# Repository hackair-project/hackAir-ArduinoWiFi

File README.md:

hackAIR is an EU-funded project aiming to develop an open technology platform for citizen observatories on air quality. Air pollution is an environmental issue with serious health and lifespan implications. However, it remains difficult for citizens to assess their exposure to air pollution and air quality issues in their country. Official air quality sensors are often few and far between, coverage is poor outside cities, and their data is not always easily accessible.

## hackAIR WiFi shield

The hackAIR WiFi shield is a do-it-yourself solution for adding wireless connectivity to an Arduino node on the cheap. It's based around a custom PCB and the ESP8266 WiFi module and it's supported by the hackAIR firmware. All the network-related work is done by the WiFi module that can be controlled by simple serial commands. The [hackAIR library for Arduino](https://github.com/hackair-project/hackAir-Arduino) contains helpful wrapper functions to make using the shield easy and simple.

### Where to order

PCBs can be ordered directly from OSHPark [here](https://oshpark.com/shared_projects/u7Z6d8GR). The source files are included in this repository so anyone can order from their manufacturer of choice. Work is being done  to make complete kits available soon.

### Documentation

Documentation for this shield is under construction [here](https://hackair-project.github.io/hackAir-Arduino/wifi/).

### Technicalities

The PCB is designed using the open source EDA called [KiCad](http://kicad-pcb.org/). The PCB render shown above is created using [PcbDraw](https://github.com/yaqwsx/PcbDraw).

### Changelog

#### Version 2.2

* Fix silkscreen of transistor Q1
* Remove footprint for ESP-12
* Add silkscreen for the programming header (pin numbers and names)

#### Version 2
 - [Add] Pull-down resistor for pin 2 (ESP Reset) so the user can flash the Arduino without jumpers
 - [Add] Silkscreen markings for pin numbers
 - [Add] Programming header for the WiFi module
 - [Del] Removed sensor I/O header used by analog sensors
 - [Del] Removed the RC filter required by some analog sensors by SHARP
 - [Fix] Move some decoupling capacitors closer to the power pads
 - [Fix] Moved the CONN_POWER and CONN_SERIAL connectors away from the USB connector of the Arduino board
 - [Fix] Fixed some acid traps in the routing
 - [Fix] Fixed the footprint of Q1 (DSG -> DGS)
 - [Fix] Changed the foorprints of all non-electrolytic caps to be wider.
 - [Fix] Fixed the silkscreen of U1 appearing on the wrong layer.

#### Version 1
Initial release

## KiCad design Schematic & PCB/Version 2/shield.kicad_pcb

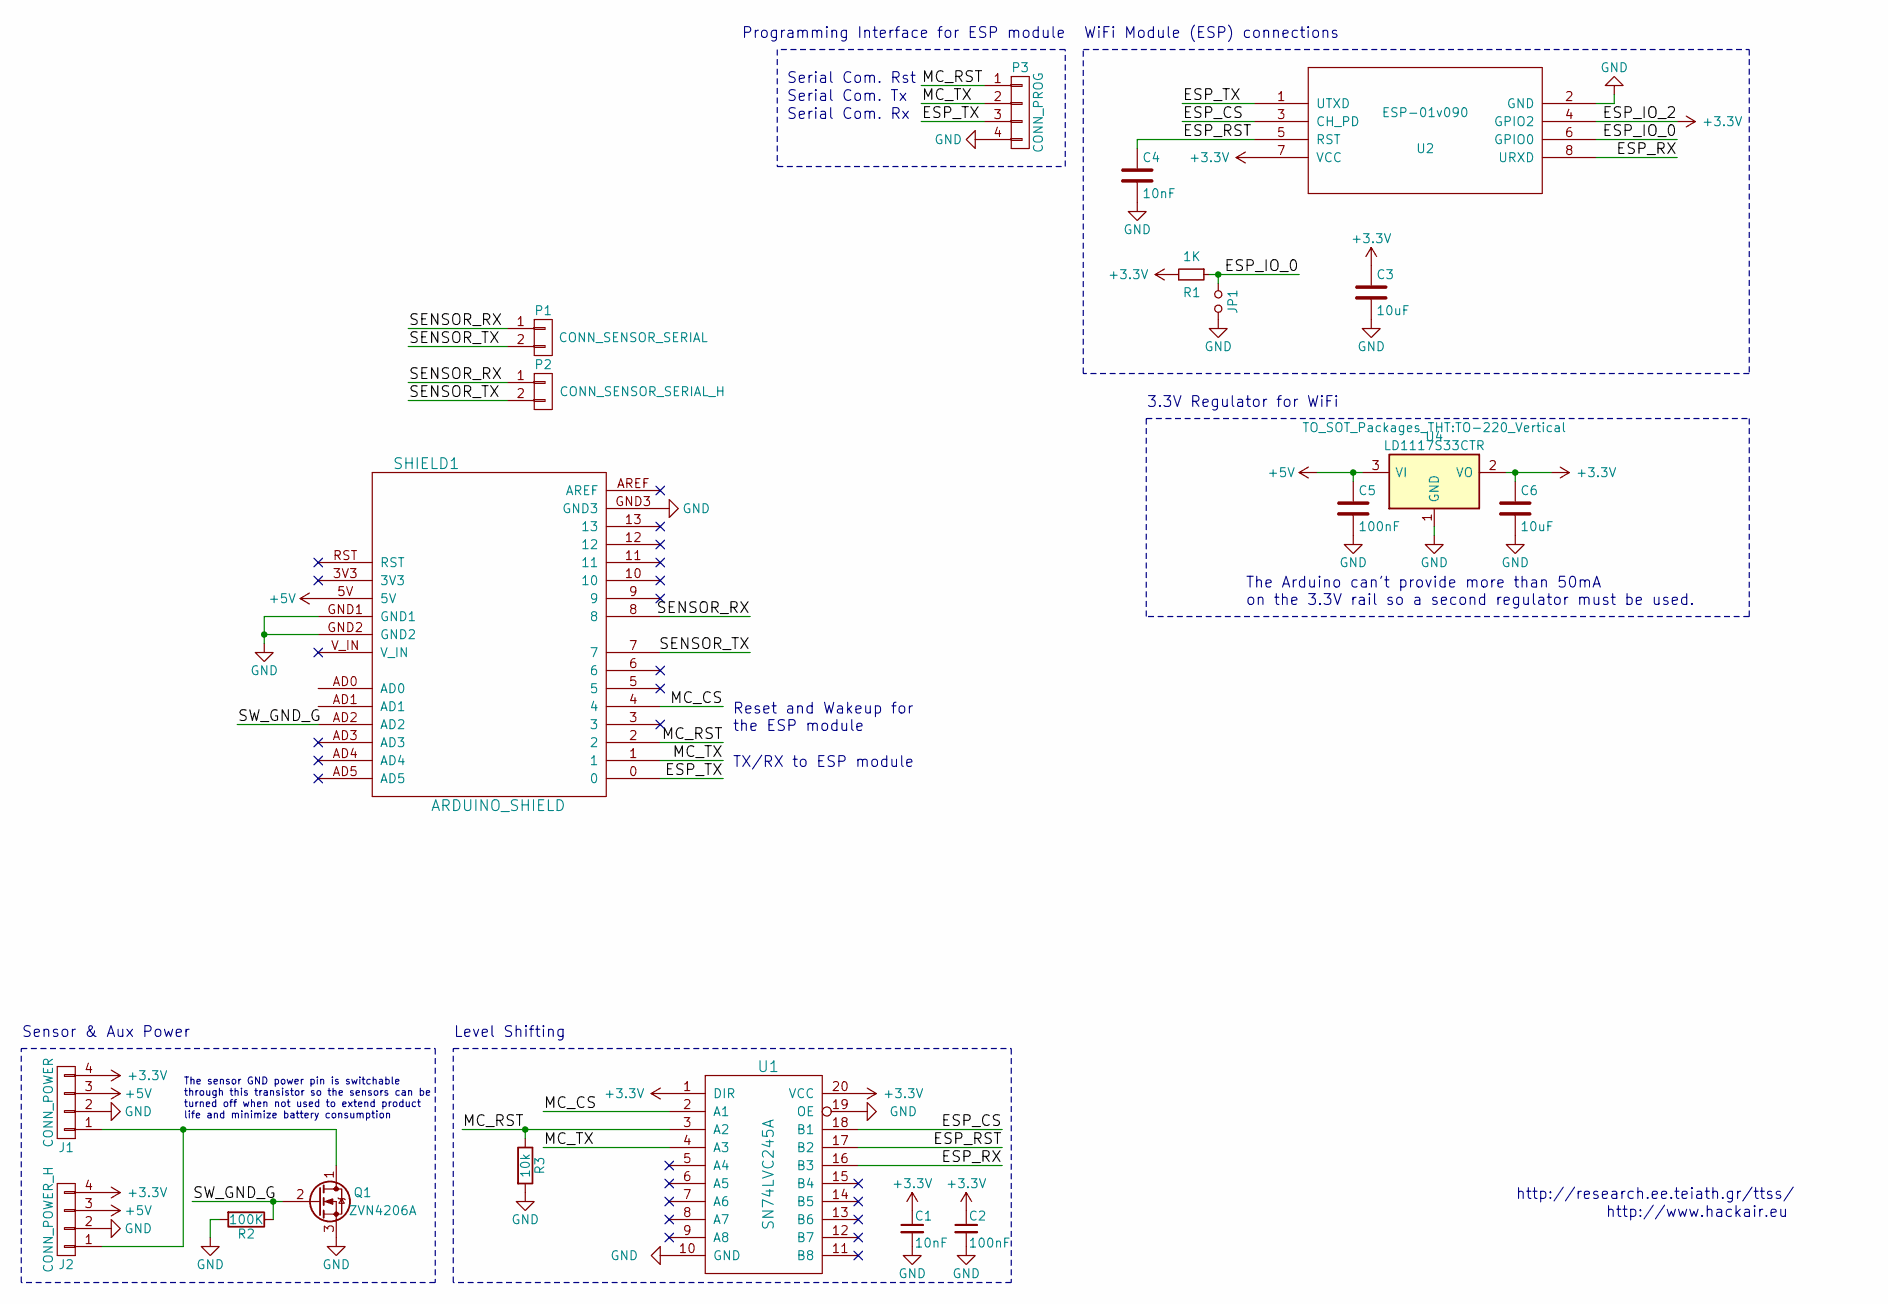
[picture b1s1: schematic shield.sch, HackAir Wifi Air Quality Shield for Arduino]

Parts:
C1, C4: 10nF; C_Disc_D6.0mm_W2.5mm_P5.00mm
C2, C5: 100nF; C_Disc_D6.0mm_W2.5mm_P5.00mm
C3, C6: 10uF; CP_Radial_D5.0mm_P2.50mm
J1: CONN_POWER; bornier4
J2: CONN_POWER_H; Pin_Header_Straight_1x04_Pitch2.54mm
JP1: Jumper_NO_Small; Pin_Header_Straight_1x02_Pitch2.54mm
P1: CONN_SENSOR_SERIAL; bornier2
P2: CONN_SENSOR_SERIAL_H; Pin_Header_Straight_1x02_Pitch2.54mm
P3: CONN_PROG; Pin_Header_Straight_1x04_Pitch2.54mm
Q1: ZVN4206A; TO-92_Inline_Wide
R1: 1K; R_Axial_DIN0207_L6.3mm_D2.5mm_P10.16mm_Horizontal
R2: 100K; R_Axial_DIN0207_L6.3mm_D2.5mm_P10.16mm_Horizontal
R3: 10k; R_Axial_DIN0207_L6.3mm_D2.5mm_P10.16mm_Horizontal
SHIELD1: ARDUINO_SHIELD; ARDUINO_SHIELD_2_040pins
U1: SN74LVC245A; DIP-20_W7.62mm_LongPads
U2: ESP-01v090; ESP-01
U4: LD1117S33CTR; TO-220_Vertical

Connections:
+3V3: C1.1, C2.1, C3.1, C6.1, J1.4, J2.4, R1.2, U1.1 (DIR), U1.20 (VCC), U2.4 (GPIO2), U2.7 (VCC), U4.2 (VO)
+5V: C5.1, J1.3, J2.3, SHIELD1.5V, U4.3 (VI)
/ESP_CS: U1.18 (B1), U2.3 (CH_PD)
/ESP_IO_0: JP1.1, R1.1, U2.6 (GPIO0)
/ESP_RST: C4.1, U1.17 (B2), U2.5 (RST)
/ESP_RX: U1.16 (B3), U2.8 (URXD)
/ESP_TX: P3.3, SHIELD1.0, U2.1 (UTXD)
/MC_CS: SHIELD1.4, U1.2 (A1)
/MC_RST: P3.1, R3.1, SHIELD1.2, U1.3 (A2)
/MC_TX: P3.2, SHIELD1.1, U1.4 (A3)
/SENSOR_RX: P1.1, P2.1, SHIELD1.8
/SENSOR_TX: P1.2, P2.2, SHIELD1.7
/SW_GND_G: Q1.2 (G), R2.1, SHIELD1.AD2
GND: C1.2, C2.2, C3.2, C4.2, C5.2, C6.2, J1.2, J2.2, JP1.2, P3.4, Q1.3 (S), R2.2, R3.2, SHIELD1.GND1, SHIELD1.GND2, SHIELD1.GND3, U1.10 (GND), U1.19 (OE), U2.2 (GND), U4.1 (GND)
unnamed: J1.1, J2.1, Q1.1 (D)

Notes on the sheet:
The Arduino can't provide more than 50mA on the 3.3V rail so a second regulator must be used.
TX/RX to ESP module
Reset and Wakeup for the ESP module
WiFi Module (ESP) connections
3.3V Regulator for WiFi
Level Shifting
http://research.ee.teiath.gr/ttss/
http://www.hackair.eu
The sensor GND power pin is switchable through this transistor so the sensors can be turned off when not used to extend product life and minimize battery consumption
Sensor & Aux Power
Serial Com. Tx
Serial Com. Rx
Serial Com. Rst
Programming Interface for ESP module

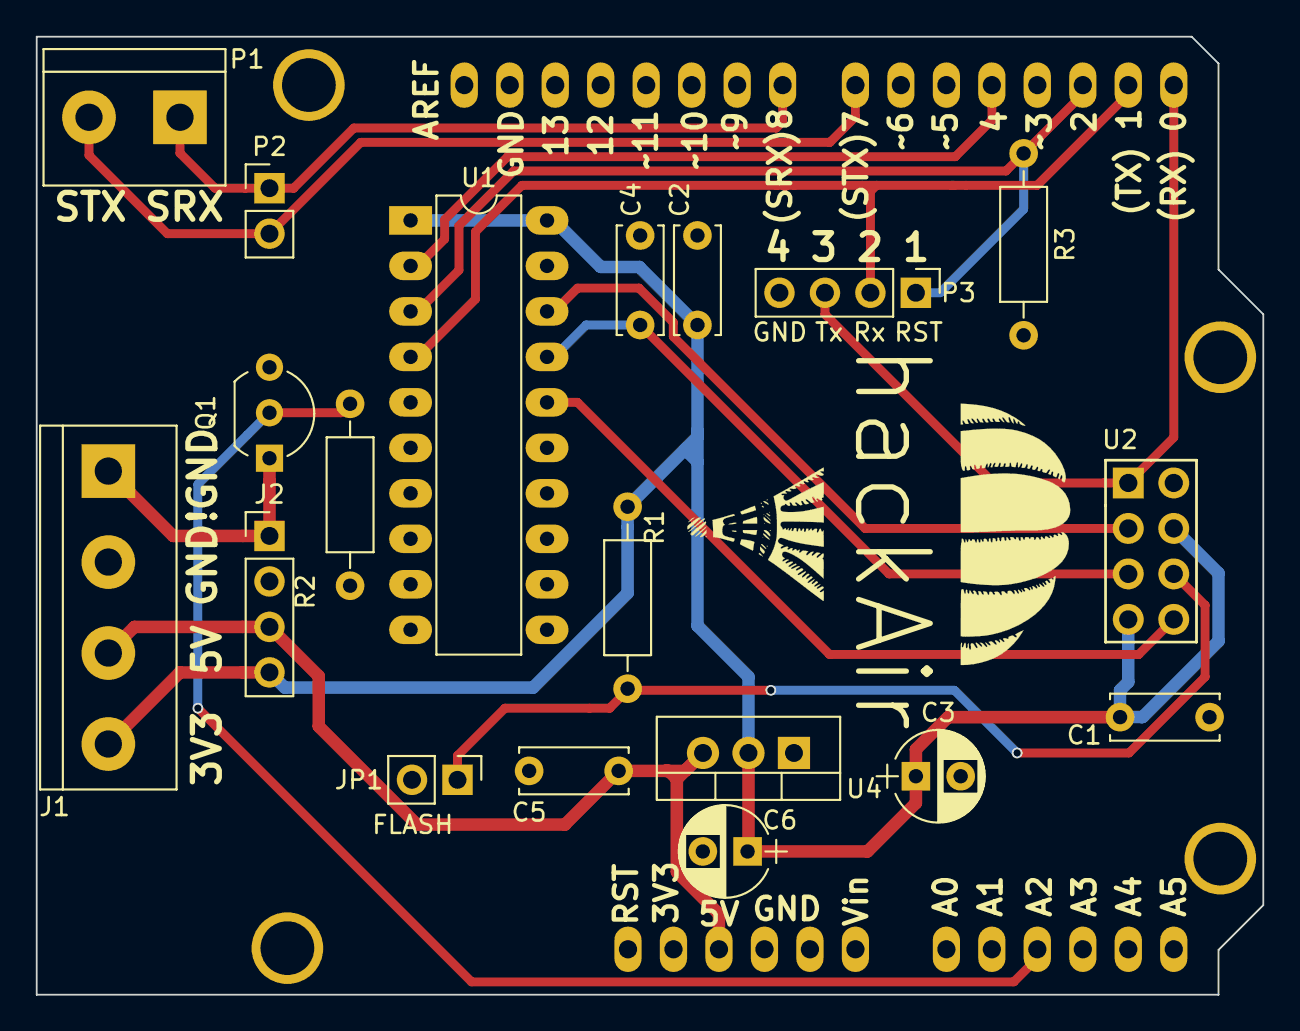
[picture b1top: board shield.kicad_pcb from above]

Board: 2 copper layers, 68.5 x 53.5 mm, 20 parts (0 on the bottom side), 15 nets.

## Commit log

2017-04-26 Update gitignore
2017-07-07 Add e+wifi command for setting the SSID/password
2017-07-07 Switch enduser_setup to manual mode so we can have our custom SSID
2017-07-07 Version bump
2017-07-09 Switch enduser_setup back to automatic mode since manual was unstable
2017-09-14 Update server_URL
    Measurements should be sent to the production server
2017-09-15 Use the production endpoint for sending data
2017-09-29 Add PCBDraw SVG drawing of the PCB
2017-11-01 Shield design revision (v2.2)

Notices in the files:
Schematic & PCB/Version 2/shield.kicad_pcb:
Part of the hackAIR project, available freely under the (CC BY 4.0) license.
kicad0ESP8266 footprints & schematic by Jerry Dunmire, CC BY-SA 4.0
Arduino Shield footprint by Nicholas C Lewis, CC BY 3.0
Schematic & PCB/Version 2/shield.sch:
kicad-ESP8266 footprints & schematic by Jerry Dunmire, CC BY-SA 4.0
